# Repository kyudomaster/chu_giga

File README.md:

# Chu Giga Project Overview

## Project goal

This project aims to create an open-source Chunithm controller using a Raspberry Pi Pico.
The hardware and overall design is heavily inspired by [WhoWeChina's chu_pico controller](https://github.com/whowechina/chu_pico).

This project also includes software that can be used with SegaTools-Compatible game dumps.

We try to fully document the design and include instructions on how to build this controller yourself.

## Current status

We have barely even gotten started lmao:

### PCB

There are first prototypes of the PCBs already, the ToF boards seem to be great, but the slider currently has the wrong pinout for LEDs so a new version needs to be made and tested.
The mainboard has not been properly tested yet and may need more power input to handle all the LEDs.

### Firmware

Basic sensor drivers exist, but require some more work.
There is no firmware for LEDs or actual input handling yet.

### Software

We only figured out that we need our own `chuniio.dll` today.

### CAD

There is a first version of the LGP panel for the slider, but nothing has been made or tested yet.
The actual case and other components also do not exist yet.

## Features

The controller uses:

- A 32-zone capacitive PCB slider. (MPR121)
- 12 ToF Air sensors. (VL53L0X)
- 3 utility buttons. (Test, Service and Coin)
- RGB Lighting for the slider. (Slider only)

## Project Scope

This repository aims to document not only the final implementation, but also the reasoning behind the design decisions. (Or lack of reasoning when that is applicable :3)

The goal is that a future contributor should be able to understand:

- How the controller works.
- Why the specific hardware was chosen.
- How the firmware is structured.
- How communication with the game works.
- How to build your own controller.

## Supported Software

The controller is intended to support:

- Chunithm cabinet dumps through segatools.
- Umiguri.
- Maybe other games... (simple keyboard output)

Additional software may be supported in the future. (The ToF sensors technically allow for 2 Axis movement.)

## Major Components

The project consists of 4 major components:

### 1. Hardware

Documentation covering:

- PCB Designs.
- Schematics.
- Component choices.
- Assembly instructions.

### 2. Mechanical Design

Documentation covering:

- CAD Files.
- Printed/CNCd parts.
- Additional parts.
- Assembly instructions.

### 3. Firmware

Firmware running on a Raspberry Pi Pico.

Responsibilities include:

- Reading sensors.
- Processing inputs.
- Managing calibration.
- Communicating with the PC.

### 4. PC Interface Software

A custom `chuniio.dll` implementation to be used with SegaTools.

Responsibilities include:

- Receiving controller input.
- Translating controller state into SegaTools-compatible input.
- Providing an interface between the controller and the game.

## Documentation

The documentation is organized into the separate major components and build, assembly and installation guides.
You can find said documentation in the [`docs`](docs/Introduction.md)

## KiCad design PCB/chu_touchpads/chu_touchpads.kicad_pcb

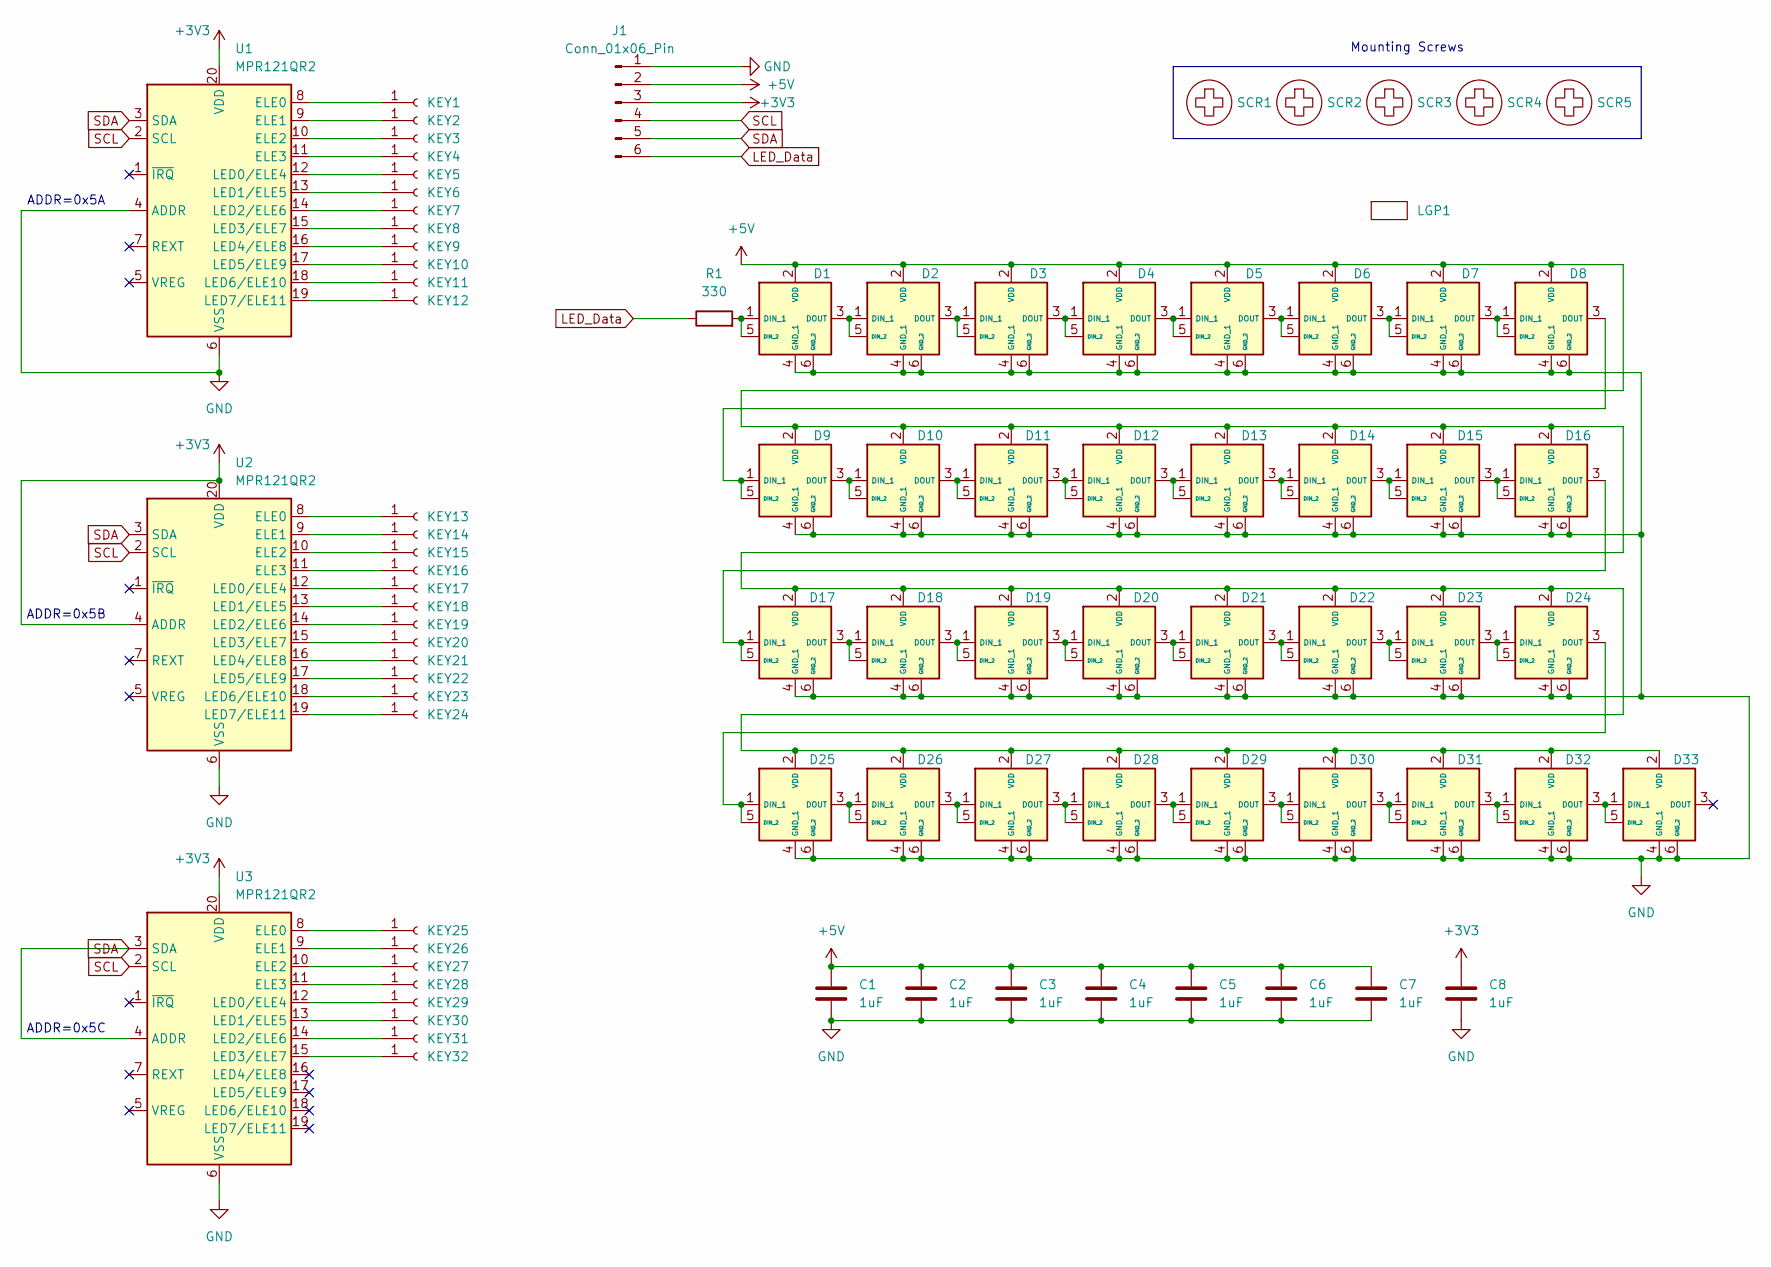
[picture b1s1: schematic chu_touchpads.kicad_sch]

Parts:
C1, C2, C3, C4, C5, C6, C7, C8: 1uF; C_0805_2012Metric_Pad1.18x1.45mm_HandSolder
D1, D2, D3, D4, D5, D6, D7, D8, D9, D10, D11, D12, D13, D14, D15, D16, D17, D18, D19, D20, D21, D22, D23, D24, D25, D26, D27, D28, D29, D30, D31, D32, D33: WS2812B; INPI42TASPRPGPB; Mouser Part Number 743-IN-PI42TASPRPGPB
J1: Conn_01x06_Pin; SHDRRA6W88P0X254_1X6_1524X254X610P
KEY1, KEY2, KEY3, KEY4, KEY5, KEY6, KEY7, KEY8, KEY9, KEY10, KEY11, KEY12, KEY13, KEY14, KEY15, KEY16, KEY17, KEY18, KEY19, KEY20, KEY21, KEY22, KEY23, KEY24, KEY25, KEY26, KEY27, KEY28, KEY29, KEY30, KEY31, KEY32: Conn_01x01_Socket; Capacitive_Touchpad_405x285
LGP1: LGP_new
R1: 330; R_0805_2012Metric_Pad1.20x1.40mm_HandSolder
SCR1, SCR2, SCR3, SCR4, SCR5: MountingHole_3.2mm_M3
U1, U2, U3: MPR121QR2; MPR121_BOARD

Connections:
+3V3: C8.1, J1.3, U1.20 (VDD), U2.4 (ADDR), U2.20 (VDD), U3.20 (VDD)
+5V: C1.1, C2.1, C3.1, C4.1, C5.1, C6.1, C7.1, D1.2 (VDD), D2.2 (VDD), D3.2 (VDD), D4.2 (VDD), D5.2 (VDD), D6.2 (VDD), D7.2 (VDD), D8.2 (VDD), D9.2 (VDD), D10.2 (VDD), D11.2 (VDD), D12.2 (VDD), D13.2 (VDD), D14.2 (VDD), D15.2 (VDD), D16.2 (VDD), D17.2 (VDD), D18.2 (VDD), D19.2 (VDD), D20.2 (VDD), D21.2 (VDD), D22.2 (VDD), D23.2 (VDD), D24.2 (VDD), D25.2 (VDD), D26.2 (VDD), D27.2 (VDD), D28.2 (VDD), D29.2 (VDD), D30.2 (VDD), D31.2 (VDD), D32.2 (VDD), D33.2 (VDD), J1.2
GND: C1.2, C2.2, C3.2, C4.2, C5.2, C6.2, C7.2, C8.2, D1.4 (GND_1), D1.6 (GND_2), D2.4 (GND_1), D2.6 (GND_2), D3.4 (GND_1), D3.6 (GND_2), D4.4 (GND_1), D4.6 (GND_2), D5.4 (GND_1), D5.6 (GND_2), D6.4 (GND_1), D6.6 (GND_2), D7.4 (GND_1), D7.6 (GND_2), D8.4 (GND_1), D8.6 (GND_2), D9.4 (GND_1), D9.6 (GND_2), D10.4 (GND_1), D10.6 (GND_2), D11.4 (GND_1), D11.6 (GND_2), D12.4 (GND_1), D12.6 (GND_2), D13.4 (GND_1), D13.6 (GND_2), D14.4 (GND_1), D14.6 (GND_2), D15.4 (GND_1), D15.6 (GND_2), D16.4 (GND_1), D16.6 (GND_2), D17.4 (GND_1), D17.6 (GND_2), D18.4 (GND_1), D18.6 (GND_2), D19.4 (GND_1), D19.6 (GND_2), D20.4 (GND_1), D20.6 (GND_2), D21.4 (GND_1), D21.6 (GND_2), D22.4 (GND_1), D22.6 (GND_2), D23.4 (GND_1), D23.6 (GND_2), D24.4 (GND_1), D24.6 (GND_2), D25.4 (GND_1), D25.6 (GND_2), D26.4 (GND_1), D26.6 (GND_2), D27.4 (GND_1), D27.6 (GND_2), D28.4 (GND_1), D28.6 (GND_2), D29.4 (GND_1), D29.6 (GND_2), D30.4 (GND_1), D30.6 (GND_2), D31.4 (GND_1), D31.6 (GND_2), D32.4 (GND_1), D32.6 (GND_2), D33.4 (GND_1), D33.6 (GND_2), J1.1, U1.4 (ADDR), U1.6 (VSS), U2.6 (VSS), U3.6 (VSS)
LED_Data: J1.6, R1.1
unnamed: D1.1 (DIN_1), D1.5 (DIN_2), R1.2
unnamed: D1.3 (DOUT), D2.1 (DIN_1), D2.5 (DIN_2)
unnamed: D2.3 (DOUT), D3.1 (DIN_1), D3.5 (DIN_2)
unnamed: D3.3 (DOUT), D4.1 (DIN_1), D4.5 (DIN_2)
unnamed: D4.3 (DOUT), D5.1 (DIN_1), D5.5 (DIN_2)
unnamed: D5.3 (DOUT), D6.1 (DIN_1), D6.5 (DIN_2)
unnamed: D6.3 (DOUT), D7.1 (DIN_1), D7.5 (DIN_2)
unnamed: D7.3 (DOUT), D8.1 (DIN_1), D8.5 (DIN_2)
unnamed: D8.3 (DOUT), D9.1 (DIN_1), D9.5 (DIN_2)
unnamed: D9.3 (DOUT), D10.1 (DIN_1), D10.5 (DIN_2)
unnamed: D10.3 (DOUT), D11.1 (DIN_1), D11.5 (DIN_2)
unnamed: D11.3 (DOUT), D12.1 (DIN_1), D12.5 (DIN_2)
unnamed: D12.3 (DOUT), D13.1 (DIN_1), D13.5 (DIN_2)
unnamed: D13.3 (DOUT), D14.1 (DIN_1), D14.5 (DIN_2)
unnamed: D14.3 (DOUT), D15.1 (DIN_1), D15.5 (DIN_2)
unnamed: D15.3 (DOUT), D16.1 (DIN_1), D16.5 (DIN_2)
unnamed: D16.3 (DOUT), D17.1 (DIN_1), D17.5 (DIN_2)
unnamed: D17.3 (DOUT), D18.1 (DIN_1), D18.5 (DIN_2)
unnamed: D18.3 (DOUT), D19.1 (DIN_1), D19.5 (DIN_2)
unnamed: D19.3 (DOUT), D20.1 (DIN_1), D20.5 (DIN_2)
unnamed: D20.3 (DOUT), D21.1 (DIN_1), D21.5 (DIN_2)
unnamed: D21.3 (DOUT), D22.1 (DIN_1), D22.5 (DIN_2)
unnamed: D22.3 (DOUT), D23.1 (DIN_1), D23.5 (DIN_2)
unnamed: D23.3 (DOUT), D24.1 (DIN_1), D24.5 (DIN_2)
unnamed: D24.3 (DOUT), D25.1 (DIN_1), D25.5 (DIN_2)
unnamed: D25.3 (DOUT), D26.1 (DIN_1), D26.5 (DIN_2)
unnamed: D26.3 (DOUT), D27.1 (DIN_1), D27.5 (DIN_2)
unnamed: D27.3 (DOUT), D28.1 (DIN_1), D28.5 (DIN_2)
unnamed: D28.3 (DOUT), D29.1 (DIN_1), D29.5 (DIN_2)
unnamed: D29.3 (DOUT), D30.1 (DIN_1), D30.5 (DIN_2)
unnamed: D30.3 (DOUT), D31.1 (DIN_1), D31.5 (DIN_2)
unnamed: D31.3 (DOUT), D32.1 (DIN_1), D32.5 (DIN_2)
unnamed: D32.3 (DOUT), D33.1 (DIN_1), D33.5 (DIN_2)
unnamed: KEY1.1 (Pin_1_1), U1.8 (ELE0)
unnamed: KEY2.1 (Pin_1_1), U1.9 (ELE1)
unnamed: KEY3.1 (Pin_1_1), U1.10 (ELE2)
unnamed: KEY4.1 (Pin_1_1), U1.11 (ELE3)
unnamed: KEY5.1 (Pin_1_1), U1.12 (LED0/ELE4)
unnamed: KEY6.1 (Pin_1_1), U1.13 (LED1/ELE5)
unnamed: KEY7.1 (Pin_1_1), U1.14 (LED2/ELE6)
unnamed: KEY8.1 (Pin_1_1), U1.15 (LED3/ELE7)
unnamed: KEY9.1 (Pin_1_1), U1.16 (LED4/ELE8)
unnamed: KEY10.1 (Pin_1_1), U1.17 (LED5/ELE9)
unnamed: KEY11.1 (Pin_1_1), U1.18 (LED6/ELE10)
unnamed: KEY12.1 (Pin_1_1), U1.19 (LED7/ELE11)
unnamed: KEY13.1 (Pin_1_1), U2.8 (ELE0)
unnamed: KEY14.1 (Pin_1_1), U2.9 (ELE1)
unnamed: KEY15.1 (Pin_1_1), U2.10 (ELE2)
unnamed: KEY16.1 (Pin_1_1), U2.11 (ELE3)
unnamed: KEY17.1 (Pin_1_1), U2.12 (LED0/ELE4)
unnamed: KEY18.1 (Pin_1_1), U2.13 (LED1/ELE5)
unnamed: KEY19.1 (Pin_1_1), U2.14 (LED2/ELE6)
unnamed: KEY20.1 (Pin_1_1), U2.15 (LED3/ELE7)
unnamed: KEY21.1 (Pin_1_1), U2.16 (LED4/ELE8)
unnamed: KEY22.1 (Pin_1_1), U2.17 (LED5/ELE9)
unnamed: KEY23.1 (Pin_1_1), U2.18 (LED6/ELE10)
unnamed: KEY24.1 (Pin_1_1), U2.19 (LED7/ELE11)
unnamed: KEY25.1 (Pin_1_1), U3.8 (ELE0)
unnamed: KEY26.1 (Pin_1_1), U3.9 (ELE1)
unnamed: KEY27.1 (Pin_1_1), U3.10 (ELE2)
unnamed: KEY28.1 (Pin_1_1), U3.11 (ELE3)
unnamed: KEY29.1 (Pin_1_1), U3.12 (LED0/ELE4)
unnamed: KEY30.1 (Pin_1_1), U3.13 (LED1/ELE5)
unnamed: KEY31.1 (Pin_1_1), U3.14 (LED2/ELE6)
unnamed: KEY32.1 (Pin_1_1), U3.15 (LED3/ELE7)
SCL: J1.4, U1.2 (SCL), U2.2 (SCL), U3.2 (SCL)
SDA: J1.5, U1.3 (SDA), U2.3 (SDA), U3.3 (SDA), U3.4 (ADDR)

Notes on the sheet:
Mounting Screws
ADDR=0x5C
ADDR=0x5A
ADDR=0x5B

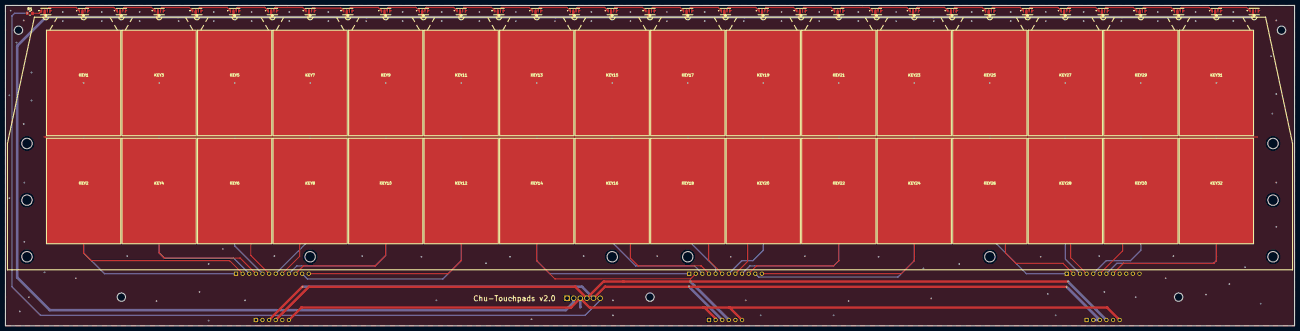
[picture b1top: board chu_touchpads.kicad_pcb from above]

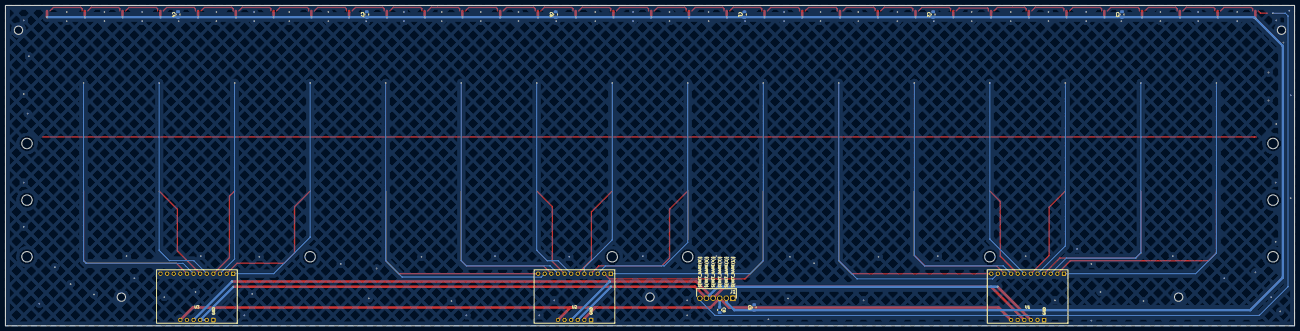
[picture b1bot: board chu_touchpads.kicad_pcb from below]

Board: 2 copper layers, 495.0 x 123.0 mm, 84 parts (12 on the bottom side), 71 nets.

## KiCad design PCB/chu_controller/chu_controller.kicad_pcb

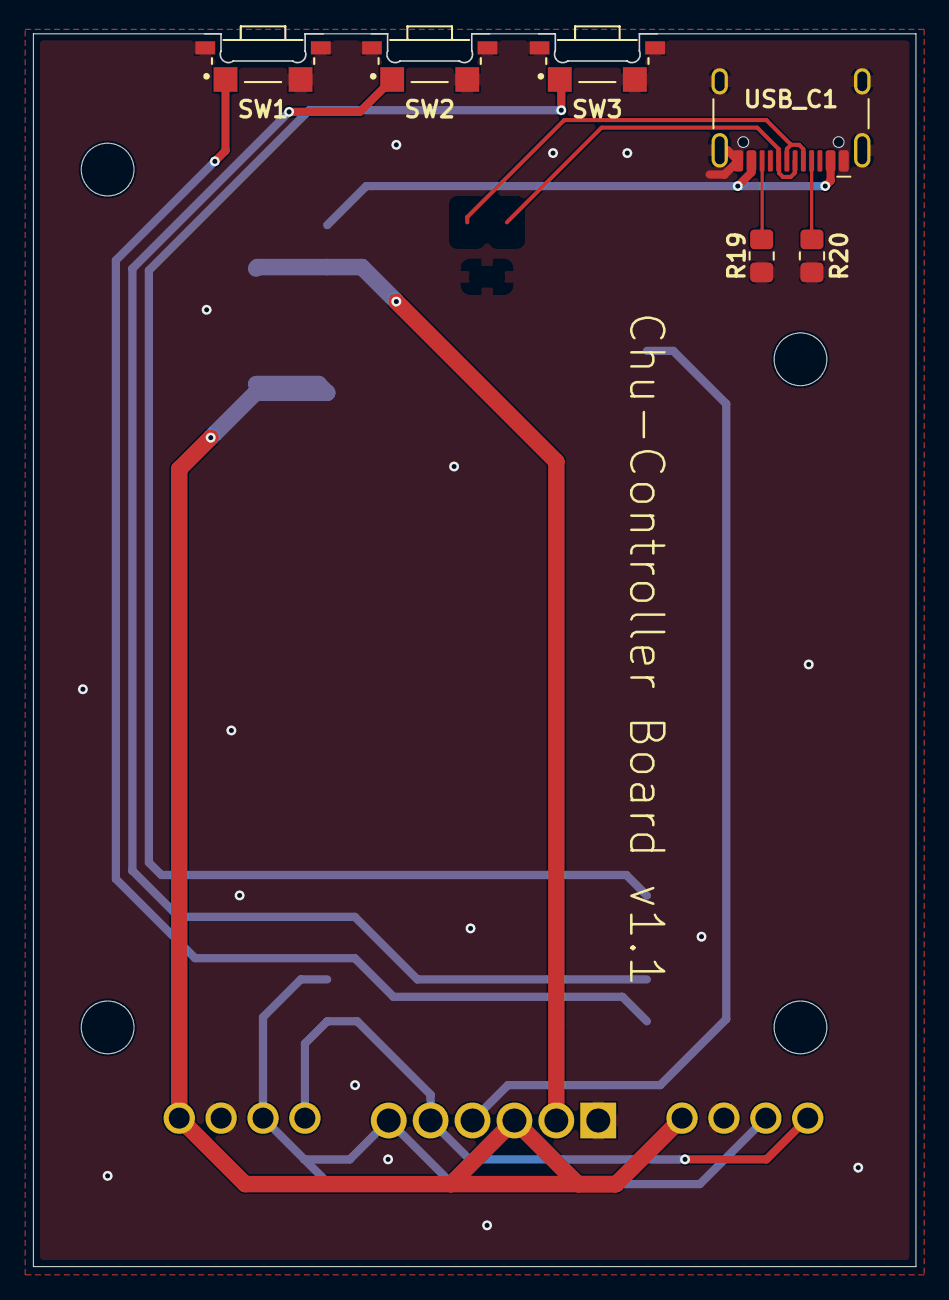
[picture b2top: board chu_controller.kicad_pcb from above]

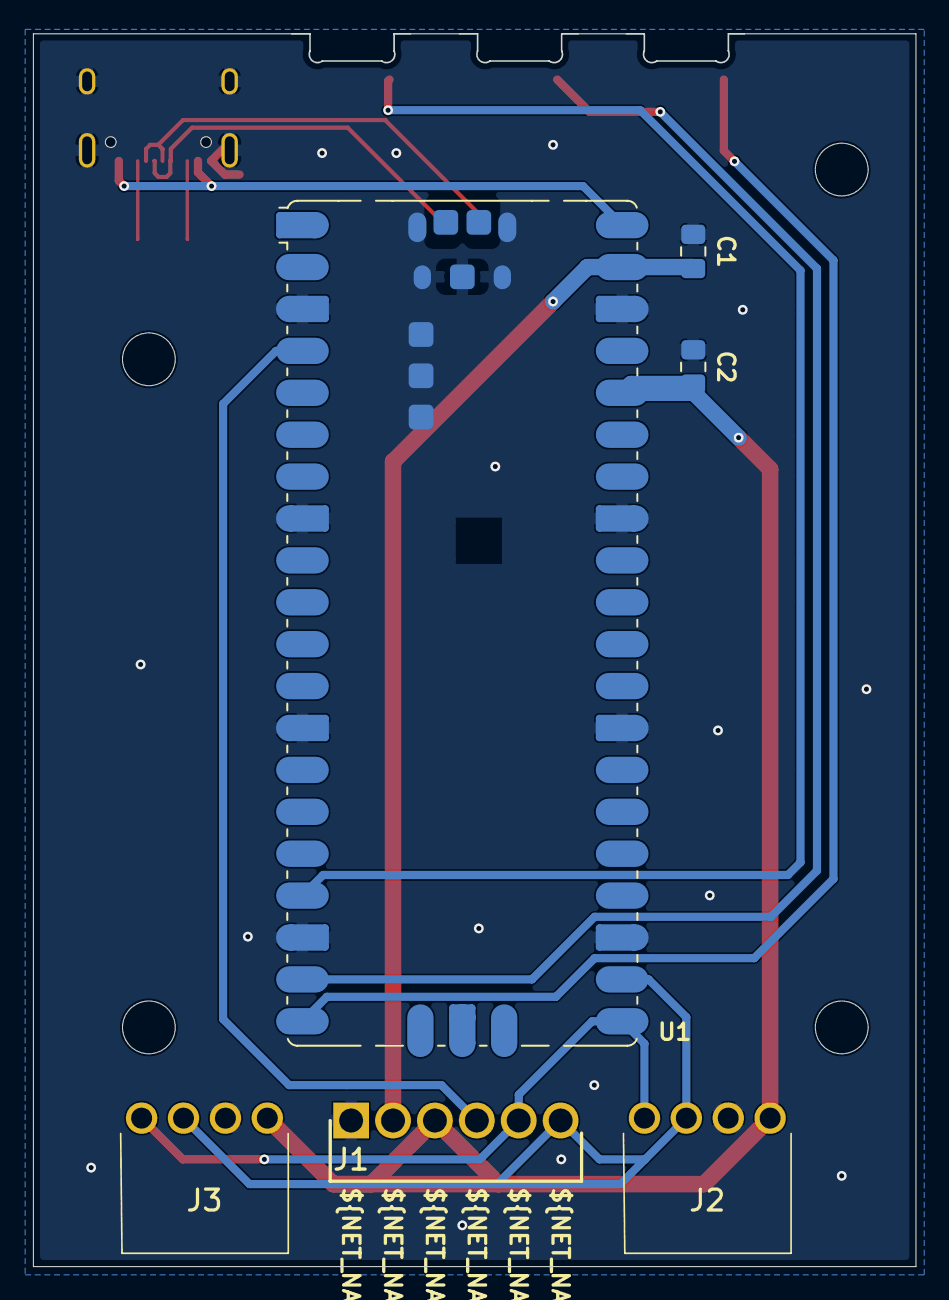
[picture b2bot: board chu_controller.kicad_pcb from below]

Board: 2 copper layers, 53.5 x 74.7 mm, 16 parts (6 on the bottom side), 14 nets.

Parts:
C1, C2: 1uF; C_0805_2012Metric_Pad1.18x1.45mm_HandSolder
J1: Conn_01x06_Pin; SHDRRA6W88P0X254_1X6_1524X254X610P
J2, J3: Conn_01x04_Pin; 6404554
R19, R20: 5K1; R_0805_2012Metric_Pad1.20x1.40mm_HandSolder
SCR1, SCR2, SCR3, SCR4: MountingHole_3.2mm_M3
SW1, SW2, SW3: SW_SPST; SW_EVQ-P46B3M
U1: RaspberryPi_Pico_Testing_pins; RaspberryPi_Pico_SMD
USB_C1: USB_C_Receptacle_HCTL_HC-TYPE-C-16P-01A

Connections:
+3V3: C2.1, J1.3, J2.1, J3.1, U1.36 (3V3)
+5V: C1.1, J1.2, U1.39 (VSYS)
/LED_Data: J1.4, U1.4 (GPIO2)
/SCL: J1.6, J2.3, J3.3, U1.22 (GPIO17)
/SDA: J1.5, J2.4, J3.4, U1.21 (GPIO16)
GND: C1.2, C2.2, J1.1, J2.2, J3.2, R19.2, R20.2, SW1.2 (B), SW1.SHIELD, SW2.2 (B), SW2.SHIELD, SW3.2 (B), SW3.SHIELD, U1.3 (GND), U1.8 (GND), U1.13 (GND), U1.18 (GND), U1.23 (GND), U1.28 (GND), U1.33 (AGND), U1.38 (GND), U1.TP1 (USB_GND), USB_C1.1 (GND), USB_C1.12 (GND), USB_C1.13 (SHIELD)
unnamed: SW1.1 (A), U1.20 (GPIO15)
unnamed: SW2.1 (A), U1.19 (GPIO14)
unnamed: SW3.1 (A), U1.17 (GPIO13)
unnamed: U1.TP2 (USB_DM), USB_C1.5 (DN2), USB_C1.7 (DN1)
unnamed: U1.TP3 (USB_DP), USB_C1.6 (DP1), USB_C1.8 (DP2)
unnamed: R20.1, USB_C1.4 (CC1)
unnamed: R19.1, USB_C1.10 (CC2)
VBUS: U1.40 (VBUS), USB_C1.2 (VBUS), USB_C1.11 (VBUS)

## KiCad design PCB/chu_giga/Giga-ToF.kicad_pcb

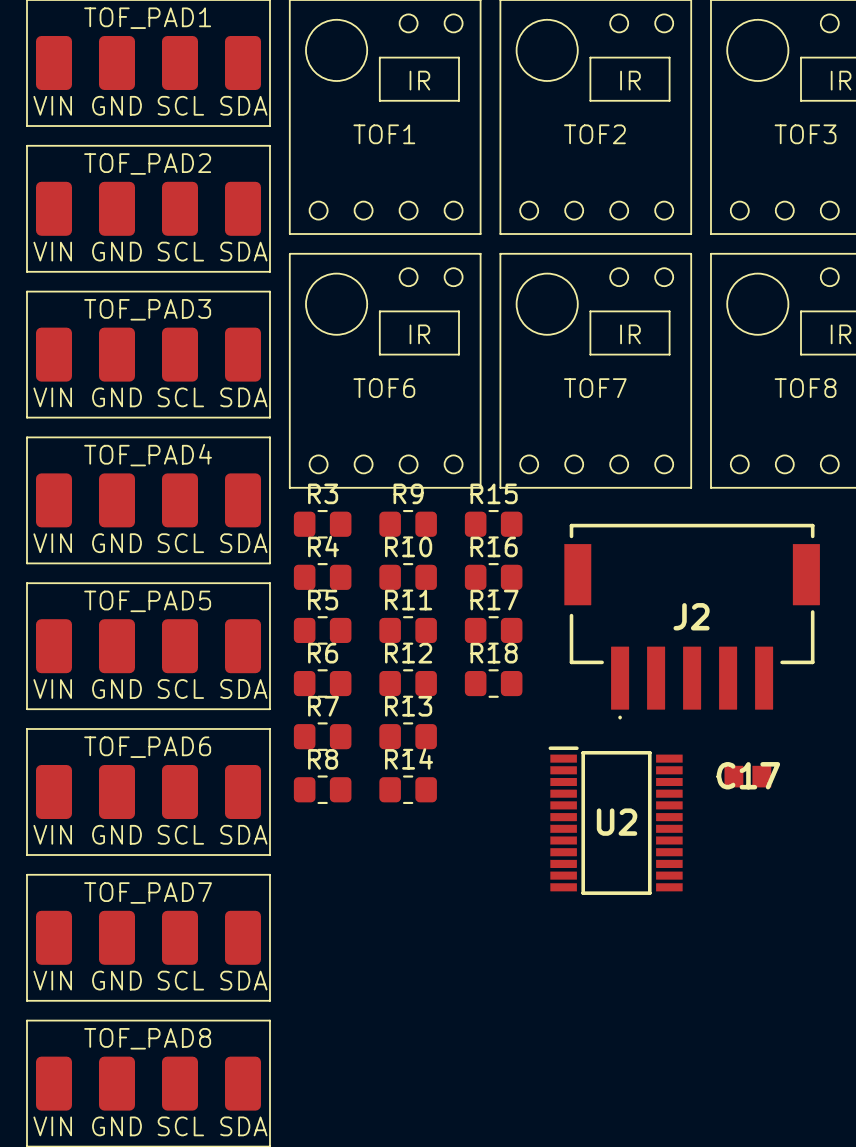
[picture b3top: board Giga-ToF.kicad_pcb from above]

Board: 2 copper layers, 35 parts (0 on the bottom side), 21 nets, no tracks yet.

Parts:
C17: 0.1uF; TMCP1E104MTRF
J2: Conn_01x05_Pin; 17754695
R3, R4, R5, R6, R7, R8, R9, R10, R11, R12, R13, R14, R15, R16, R17, R18: 5K1; R_0805_2012Metric_Pad1.20x1.40mm_HandSolder
TOF1, TOF2, TOF3, TOF4, TOF5, TOF6, TOF7, TOF8: GY530 ToF Sensor board
TOF_PAD1, TOF_PAD2, TOF_PAD3, TOF_PAD4, TOF_PAD5, TOF_PAD6, TOF_PAD7, TOF_PAD8: ToF Wiring Pad
U2: TCA9548APWR; SOP65P640X120-24N

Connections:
+3V3: C17.1, J2.1, R3.1, R4.1, R5.1, R6.1, R7.1, R8.1, R9.1, R10.1, R11.1, R12.1, R13.1, R14.1, R15.1, R16.1, R17.1, R18.1, TOF_PAD1.1 (VIN), TOF_PAD2.1 (VIN), TOF_PAD3.1 (VIN), TOF_PAD4.1 (VIN), TOF_PAD5.1 (VIN), TOF_PAD6.1 (VIN), TOF_PAD7.1 (VIN), TOF_PAD8.1 (VIN), U2.24 (VCC)
/Controller/SCL: J2.3, U2.22 (SCL)
/Controller/SDA: J2.4, U2.23 (SDA)
/Controller/ToF_Reset: J2.5, U2.3 (~RESET)
/Time-Of-Flight sensors/SCL_1: R3.2, TOF_PAD1.3 (SCL), U2.5 (SC0)
/Time-Of-Flight sensors/SCL_2: R5.2, TOF_PAD2.3 (SCL), U2.7 (SC1)
/Time-Of-Flight sensors/SCL_3: R7.2, TOF_PAD3.3 (SCL), U2.9 (SC2)
/Time-Of-Flight sensors/SCL_4: R9.2, TOF_PAD4.3 (SCL), U2.11 (SC3)
/Time-Of-Flight sensors/SCL_5: R11.2, TOF_PAD5.3 (SCL), U2.14 (SC4)
/Time-Of-Flight sensors/SCL_6: R13.2, TOF_PAD6.3 (SCL), U2.16 (SC5)
/Time-Of-Flight sensors/SCL_7: R15.2, TOF_PAD7.3 (SCL), U2.18 (SC6)
/Time-Of-Flight sensors/SCL_8: R17.2, TOF_PAD8.3 (SCL), U2.20 (SC7)
/Time-Of-Flight sensors/SDA_1: R4.2, TOF_PAD1.4 (SDA), U2.4 (SD0)
/Time-Of-Flight sensors/SDA_2: R6.2, TOF_PAD2.4 (SDA), U2.6 (SD1)
/Time-Of-Flight sensors/SDA_3: R8.2, TOF_PAD3.4 (SDA), U2.8 (SD2)
/Time-Of-Flight sensors/SDA_4: R10.2, TOF_PAD4.4 (SDA), U2.10 (SD3)
/Time-Of-Flight sensors/SDA_5: R12.2, TOF_PAD5.4 (SDA), U2.13 (SD4)
/Time-Of-Flight sensors/SDA_6: R14.2, TOF_PAD6.4 (SDA), U2.15 (SD5)
/Time-Of-Flight sensors/SDA_7: R16.2, TOF_PAD7.4 (SDA), U2.17 (SD6)
/Time-Of-Flight sensors/SDA_8: R18.2, TOF_PAD8.4 (SDA), U2.19 (SD7)
GND: C17.2, J2.2, TOF_PAD1.2 (GND), TOF_PAD2.2 (GND), TOF_PAD3.2 (GND), TOF_PAD4.2 (GND), TOF_PAD5.2 (GND), TOF_PAD6.2 (GND), TOF_PAD7.2 (GND), TOF_PAD8.2 (GND), U2.1 (A0), U2.2 (A1), U2.12 (GND), U2.21 (A2)

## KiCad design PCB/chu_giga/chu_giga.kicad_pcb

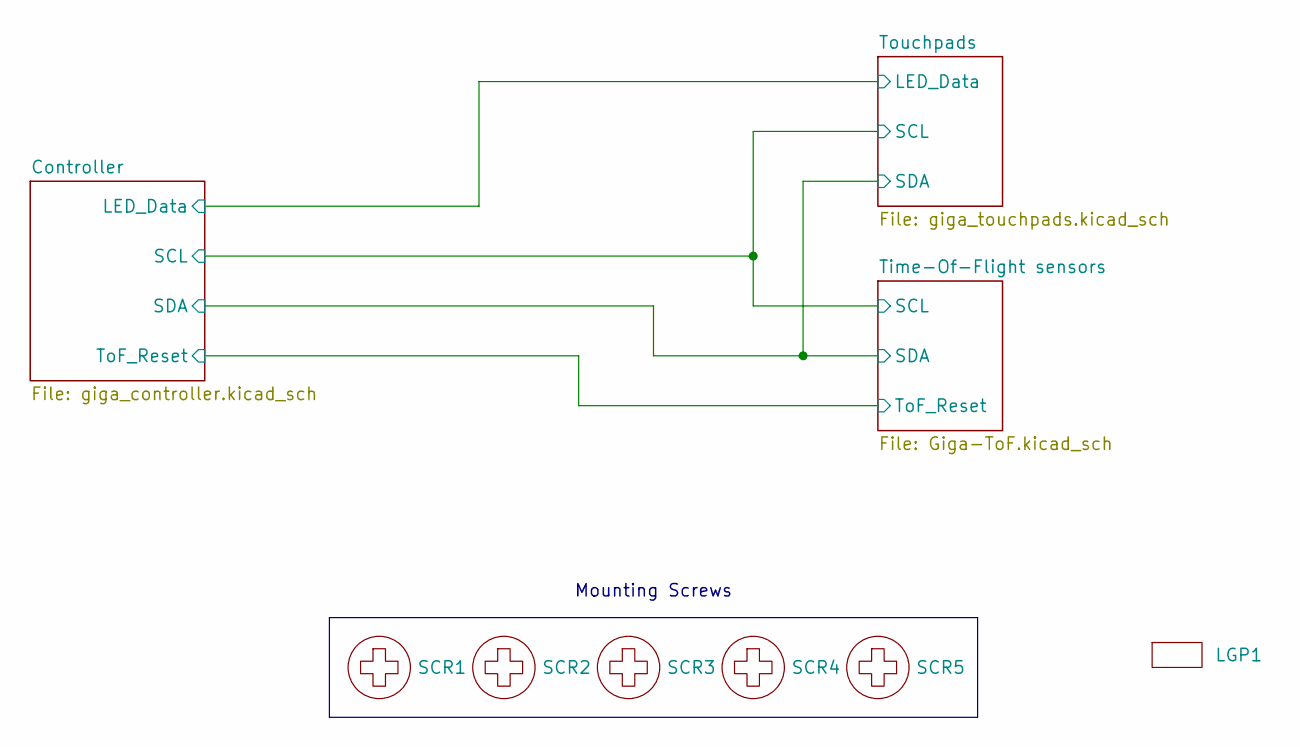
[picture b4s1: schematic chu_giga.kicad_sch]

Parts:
LGP1: LGP_new
SCR1, SCR2, SCR3, SCR4, SCR5: MountingHole_3.2mm_M3

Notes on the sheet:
Mounting Screws

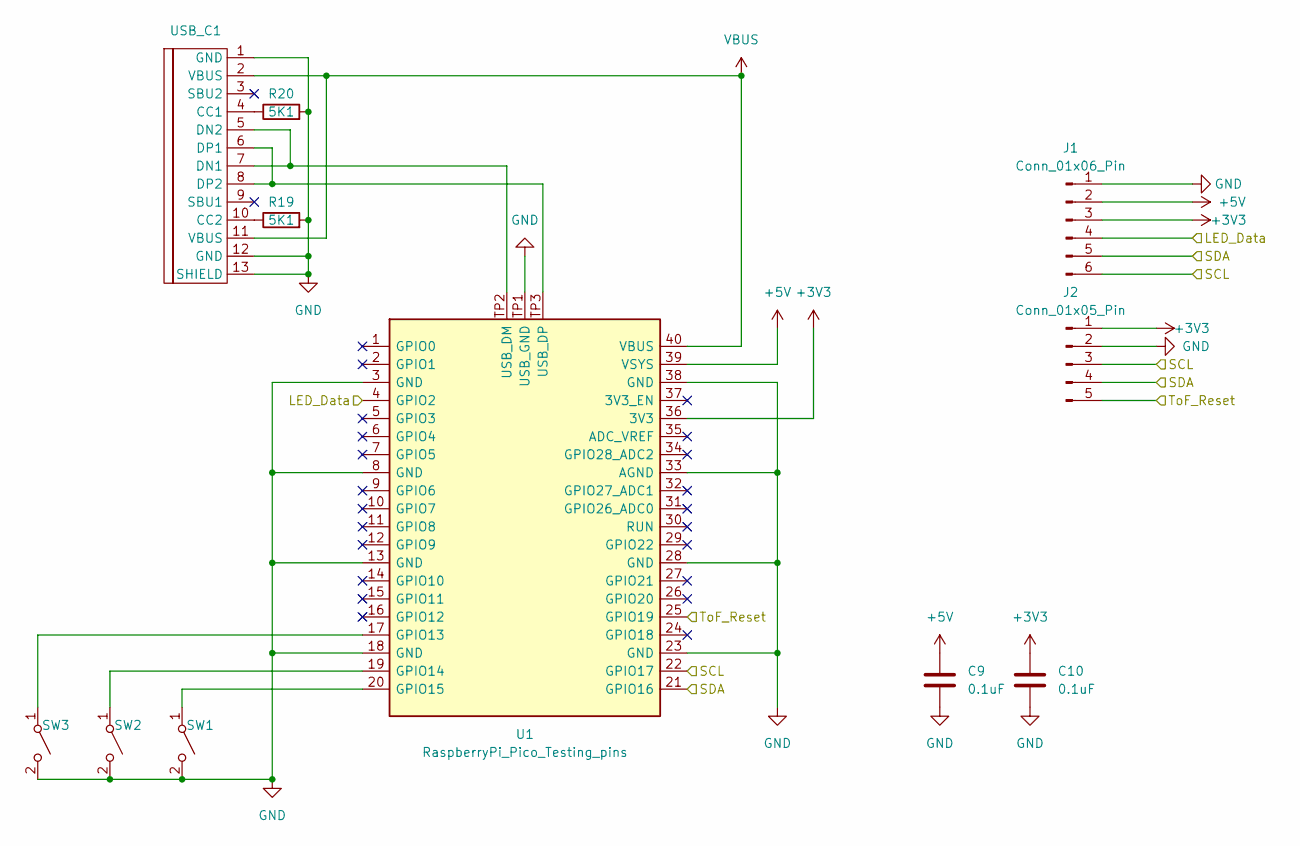
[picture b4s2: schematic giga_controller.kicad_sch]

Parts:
C9, C10: 0.1uF; TMCP1E104MTRF
J1: Conn_01x06_Pin; 17754696
J2: Conn_01x05_Pin; 17754695
R19, R20: 5K1; R_0805_2012Metric_Pad1.20x1.40mm_HandSolder
SW1, SW2, SW3: SW_SPST; SW_EVQ-P46B3M
U1: RaspberryPi_Pico_Testing_pins; RaspberryPi_Pico_SMD
USB_C1: USB_C_Receptacle_HCTL_HC-TYPE-C-16P-01A

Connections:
+3V3: C10.1, J1.3, J2.1, U1.36 (3V3); also elsewhere on the board
+5V: C9.1, J1.2, U1.39 (VSYS); also elsewhere on the board
/Controller/LED_Data: J1.4, U1.4 (GPIO2); also elsewhere on the board
/Controller/SCL: J1.6, J2.3, U1.22 (GPIO17); also elsewhere on the board
/Controller/SDA: J1.5, J2.4, U1.21 (GPIO16); also elsewhere on the board
/Controller/ToF_Reset: J2.5, U1.25 (GPIO19); also elsewhere on the board
GND: C9.2, C10.2, J1.1, J2.2, R19.2, R20.2, SW1.2 (B), SW2.2 (B), SW3.2 (B), U1.3 (GND), U1.8 (GND), U1.13 (GND), U1.18 (GND), U1.23 (GND), U1.28 (GND), U1.33 (AGND), U1.38 (GND), U1.TP1 (USB_GND), USB_C1.1 (GND), USB_C1.12 (GND), USB_C1.13 (SHIELD); also elsewhere on the board
unnamed: SW1.1 (A), U1.20 (GPIO15)
unnamed: SW2.1 (A), U1.19 (GPIO14)
unnamed: SW3.1 (A), U1.17 (GPIO13)
unnamed: U1.TP2 (USB_DM), USB_C1.5 (DN2), USB_C1.7 (DN1)
unnamed: U1.TP3 (USB_DP), USB_C1.6 (DP1), USB_C1.8 (DP2)
unnamed: R20.1, USB_C1.4 (CC1)
unnamed: R19.1, USB_C1.10 (CC2)
VBUS: U1.40 (VBUS), USB_C1.2 (VBUS), USB_C1.11 (VBUS)

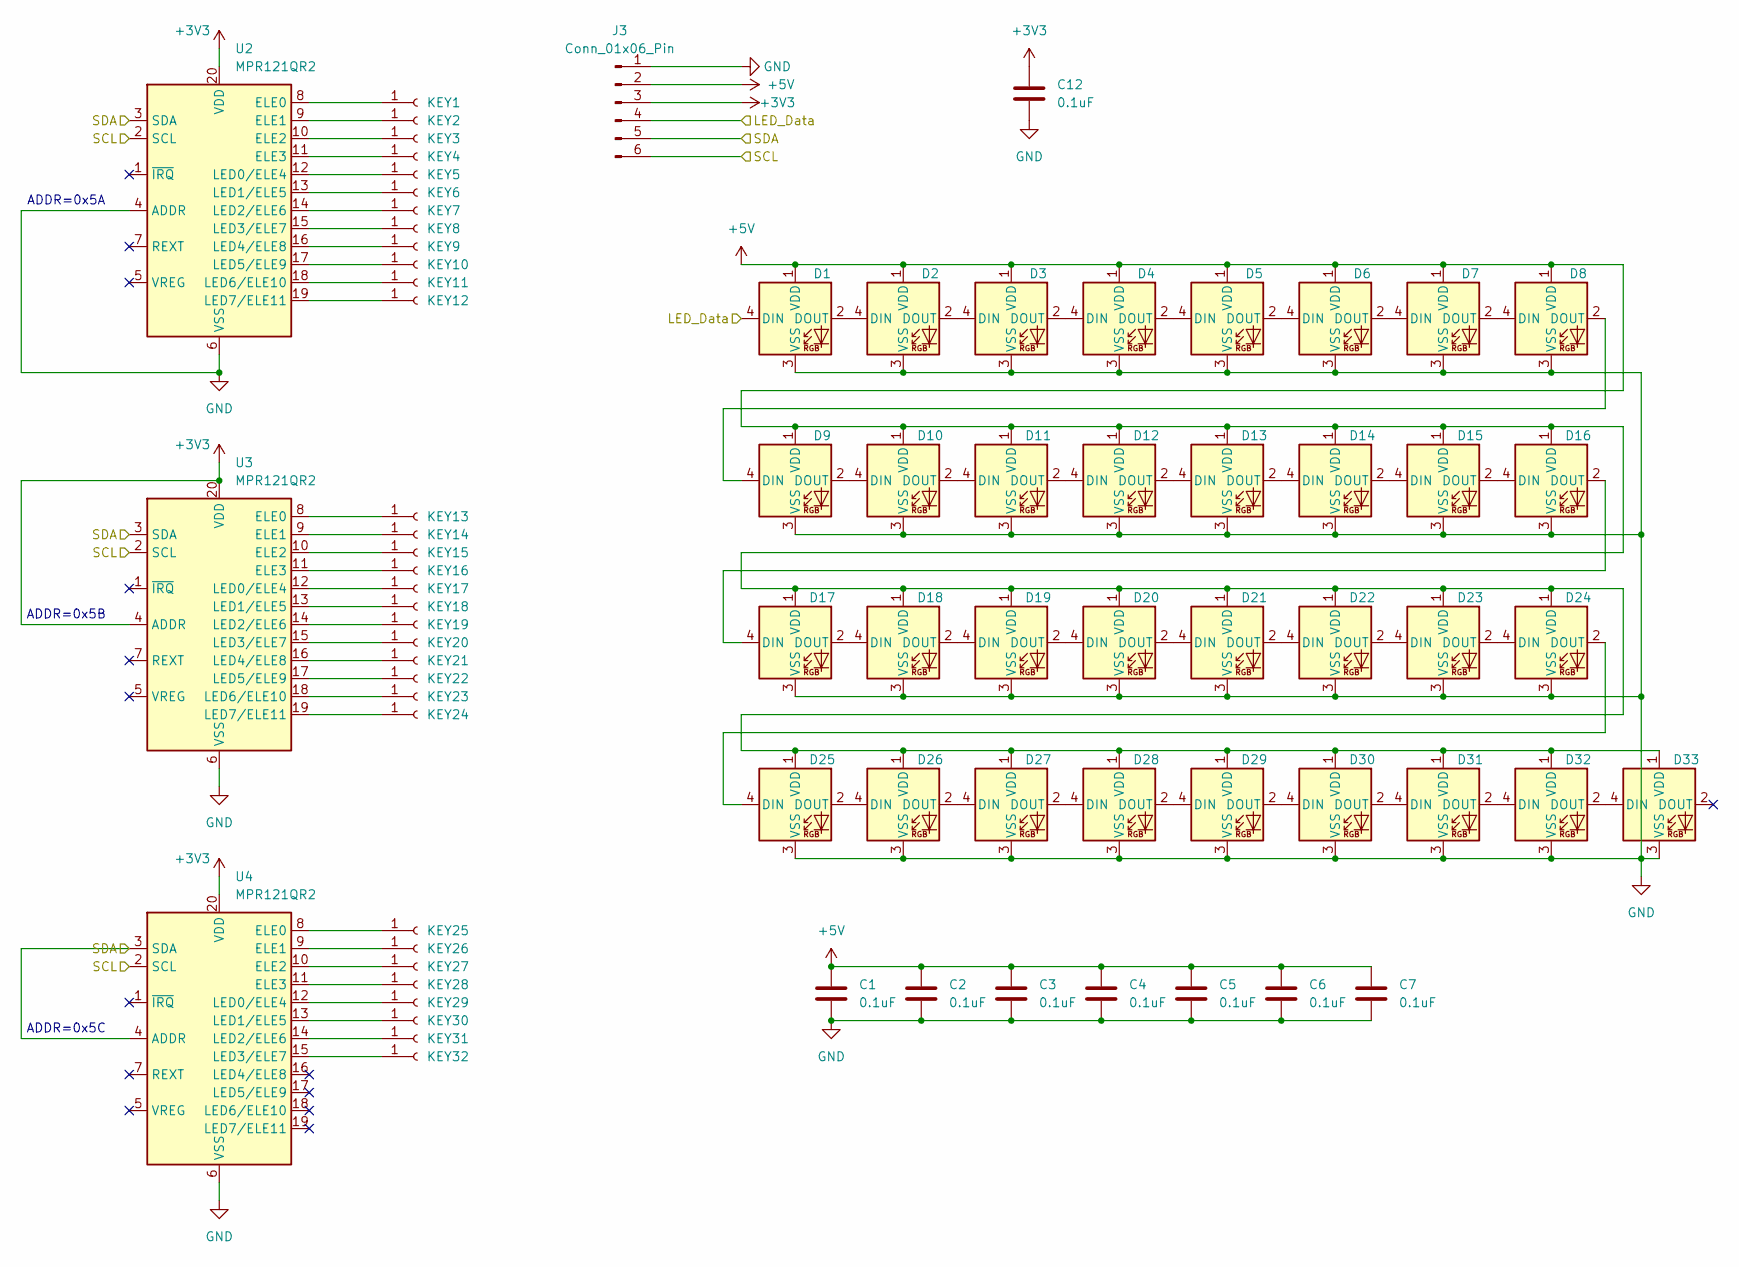
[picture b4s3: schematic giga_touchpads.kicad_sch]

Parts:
C1, C2, C3, C4, C5, C6, C7, C12: 0.1uF; TMCP1E104MTRF
D1, D2, D3, D4, D5, D6, D7, D8, D9, D10, D11, D12, D13, D14, D15, D16, D17, D18, D19, D20, D21, D22, D23, D24, D25, D26, D27, D28, D29, D30, D31, D32, D33: WS2812B; INPI42TASPRPGPB
J3: Conn_01x06_Pin; 17754696
KEY1, KEY2, KEY3, KEY4, KEY5, KEY6, KEY7, KEY8, KEY9, KEY10, KEY11, KEY12, KEY13, KEY14, KEY15, KEY16, KEY17, KEY18, KEY19, KEY20, KEY21, KEY22, KEY23, KEY24, KEY25, KEY26, KEY27, KEY28, KEY29, KEY30, KEY31, KEY32: Conn_01x01_Socket; Capacitive_Touchpad_405x285
U2, U3, U4: MPR121QR2; MPR121_BOARD

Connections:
+3V3: C12.1, J3.3, U2.20 (VDD), U3.4 (ADDR), U3.20 (VDD), U4.20 (VDD); also elsewhere on the board
+5V: C1.1, C2.1, C3.1, C4.1, C5.1, C6.1, C7.1, D1.1 (VDD), D2.1 (VDD), D3.1 (VDD), D4.1 (VDD), D5.1 (VDD), D6.1 (VDD), D7.1 (VDD), D8.1 (VDD), D9.1 (VDD), D10.1 (VDD), D11.1 (VDD), D12.1 (VDD), D13.1 (VDD), D14.1 (VDD), D15.1 (VDD), D16.1 (VDD), D17.1 (VDD), D18.1 (VDD), D19.1 (VDD), D20.1 (VDD), D21.1 (VDD), D22.1 (VDD), D23.1 (VDD), D24.1 (VDD), D25.1 (VDD), D26.1 (VDD), D27.1 (VDD), D28.1 (VDD), D29.1 (VDD), D30.1 (VDD), D31.1 (VDD), D32.1 (VDD), D33.1 (VDD), J3.2; also elsewhere on the board
/Controller/LED_Data: D1.4 (DIN), J3.4; also elsewhere on the board
/Controller/SCL: J3.6, U2.2 (SCL), U3.2 (SCL), U4.2 (SCL); also elsewhere on the board
/Controller/SDA: J3.5, U2.3 (SDA), U3.3 (SDA), U4.3 (SDA), U4.4 (ADDR); also elsewhere on the board
GND: C1.2, C2.2, C3.2, C4.2, C5.2, C6.2, C7.2, C12.2, D1.3 (VSS), D2.3 (VSS), D3.3 (VSS), D4.3 (VSS), D5.3 (VSS), D6.3 (VSS), D7.3 (VSS), D8.3 (VSS), D9.3 (VSS), D10.3 (VSS), D11.3 (VSS), D12.3 (VSS), D13.3 (VSS), D14.3 (VSS), D15.3 (VSS), D16.3 (VSS), D17.3 (VSS), D18.3 (VSS), D19.3 (VSS), D20.3 (VSS), D21.3 (VSS), D22.3 (VSS), D23.3 (VSS), D24.3 (VSS), D25.3 (VSS), D26.3 (VSS), D27.3 (VSS), D28.3 (VSS), D29.3 (VSS), D30.3 (VSS), D31.3 (VSS), D32.3 (VSS), D33.3 (VSS), J3.1, U2.4 (ADDR), U2.6 (VSS), U3.6 (VSS), U4.6 (VSS); also elsewhere on the board
unnamed: D1.2 (DOUT), D2.4 (DIN)
unnamed: D2.2 (DOUT), D3.4 (DIN)
unnamed: D3.2 (DOUT), D4.4 (DIN)
unnamed: D4.2 (DOUT), D5.4 (DIN)
unnamed: D5.2 (DOUT), D6.4 (DIN)
unnamed: D6.2 (DOUT), D7.4 (DIN)
unnamed: D7.2 (DOUT), D8.4 (DIN)
unnamed: D8.2 (DOUT), D9.4 (DIN)
unnamed: D9.2 (DOUT), D10.4 (DIN)
unnamed: D10.2 (DOUT), D11.4 (DIN)
unnamed: D11.2 (DOUT), D12.4 (DIN)
unnamed: D12.2 (DOUT), D13.4 (DIN)
unnamed: D13.2 (DOUT), D14.4 (DIN)
unnamed: D14.2 (DOUT), D15.4 (DIN)
unnamed: D15.2 (DOUT), D16.4 (DIN)
unnamed: D16.2 (DOUT), D17.4 (DIN)
unnamed: D17.2 (DOUT), D18.4 (DIN)
unnamed: D18.2 (DOUT), D19.4 (DIN)
unnamed: D19.2 (DOUT), D20.4 (DIN)
unnamed: D20.2 (DOUT), D21.4 (DIN)
unnamed: D21.2 (DOUT), D22.4 (DIN)
unnamed: D22.2 (DOUT), D23.4 (DIN)
unnamed: D23.2 (DOUT), D24.4 (DIN)
unnamed: D24.2 (DOUT), D25.4 (DIN)
unnamed: D25.2 (DOUT), D26.4 (DIN)
unnamed: D26.2 (DOUT), D27.4 (DIN)
unnamed: D27.2 (DOUT), D28.4 (DIN)
unnamed: D28.2 (DOUT), D29.4 (DIN)
unnamed: D29.2 (DOUT), D30.4 (DIN)
unnamed: D30.2 (DOUT), D31.4 (DIN)
unnamed: D31.2 (DOUT), D32.4 (DIN)
unnamed: D32.2 (DOUT), D33.4 (DIN)
unnamed: KEY1.1 (Pin_1_1), U2.8 (ELE0)
unnamed: KEY2.1 (Pin_1_1), U2.9 (ELE1)
unnamed: KEY3.1 (Pin_1_1), U2.10 (ELE2)
unnamed: KEY4.1 (Pin_1_1), U2.11 (ELE3)
unnamed: KEY5.1 (Pin_1_1), U2.12 (LED0/ELE4)
unnamed: KEY6.1 (Pin_1_1), U2.13 (LED1/ELE5)
unnamed: KEY7.1 (Pin_1_1), U2.14 (LED2/ELE6)
unnamed: KEY8.1 (Pin_1_1), U2.15 (LED3/ELE7)
unnamed: KEY9.1 (Pin_1_1), U2.16 (LED4/ELE8)
unnamed: KEY10.1 (Pin_1_1), U2.17 (LED5/ELE9)
unnamed: KEY11.1 (Pin_1_1), U2.18 (LED6/ELE10)
unnamed: KEY12.1 (Pin_1_1), U2.19 (LED7/ELE11)
unnamed: KEY13.1 (Pin_1_1), U3.8 (ELE0)
unnamed: KEY14.1 (Pin_1_1), U3.9 (ELE1)
unnamed: KEY15.1 (Pin_1_1), U3.10 (ELE2)
unnamed: KEY16.1 (Pin_1_1), U3.11 (ELE3)
unnamed: KEY17.1 (Pin_1_1), U3.12 (LED0/ELE4)
unnamed: KEY18.1 (Pin_1_1), U3.13 (LED1/ELE5)
unnamed: KEY19.1 (Pin_1_1), U3.14 (LED2/ELE6)
unnamed: KEY20.1 (Pin_1_1), U3.15 (LED3/ELE7)
unnamed: KEY21.1 (Pin_1_1), U3.16 (LED4/ELE8)
unnamed: KEY22.1 (Pin_1_1), U3.17 (LED5/ELE9)
unnamed: KEY23.1 (Pin_1_1), U3.18 (LED6/ELE10)
unnamed: KEY24.1 (Pin_1_1), U3.19 (LED7/ELE11)
unnamed: KEY25.1 (Pin_1_1), U4.8 (ELE0)
unnamed: KEY26.1 (Pin_1_1), U4.9 (ELE1)
unnamed: KEY27.1 (Pin_1_1), U4.10 (ELE2)
unnamed: KEY28.1 (Pin_1_1), U4.11 (ELE3)
unnamed: KEY29.1 (Pin_1_1), U4.12 (LED0/ELE4)
unnamed: KEY30.1 (Pin_1_1), U4.13 (LED1/ELE5)
unnamed: KEY31.1 (Pin_1_1), U4.14 (LED2/ELE6)
unnamed: KEY32.1 (Pin_1_1), U4.15 (LED3/ELE7)

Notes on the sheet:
ADDR=0x5C
ADDR=0x5A
ADDR=0x5B
